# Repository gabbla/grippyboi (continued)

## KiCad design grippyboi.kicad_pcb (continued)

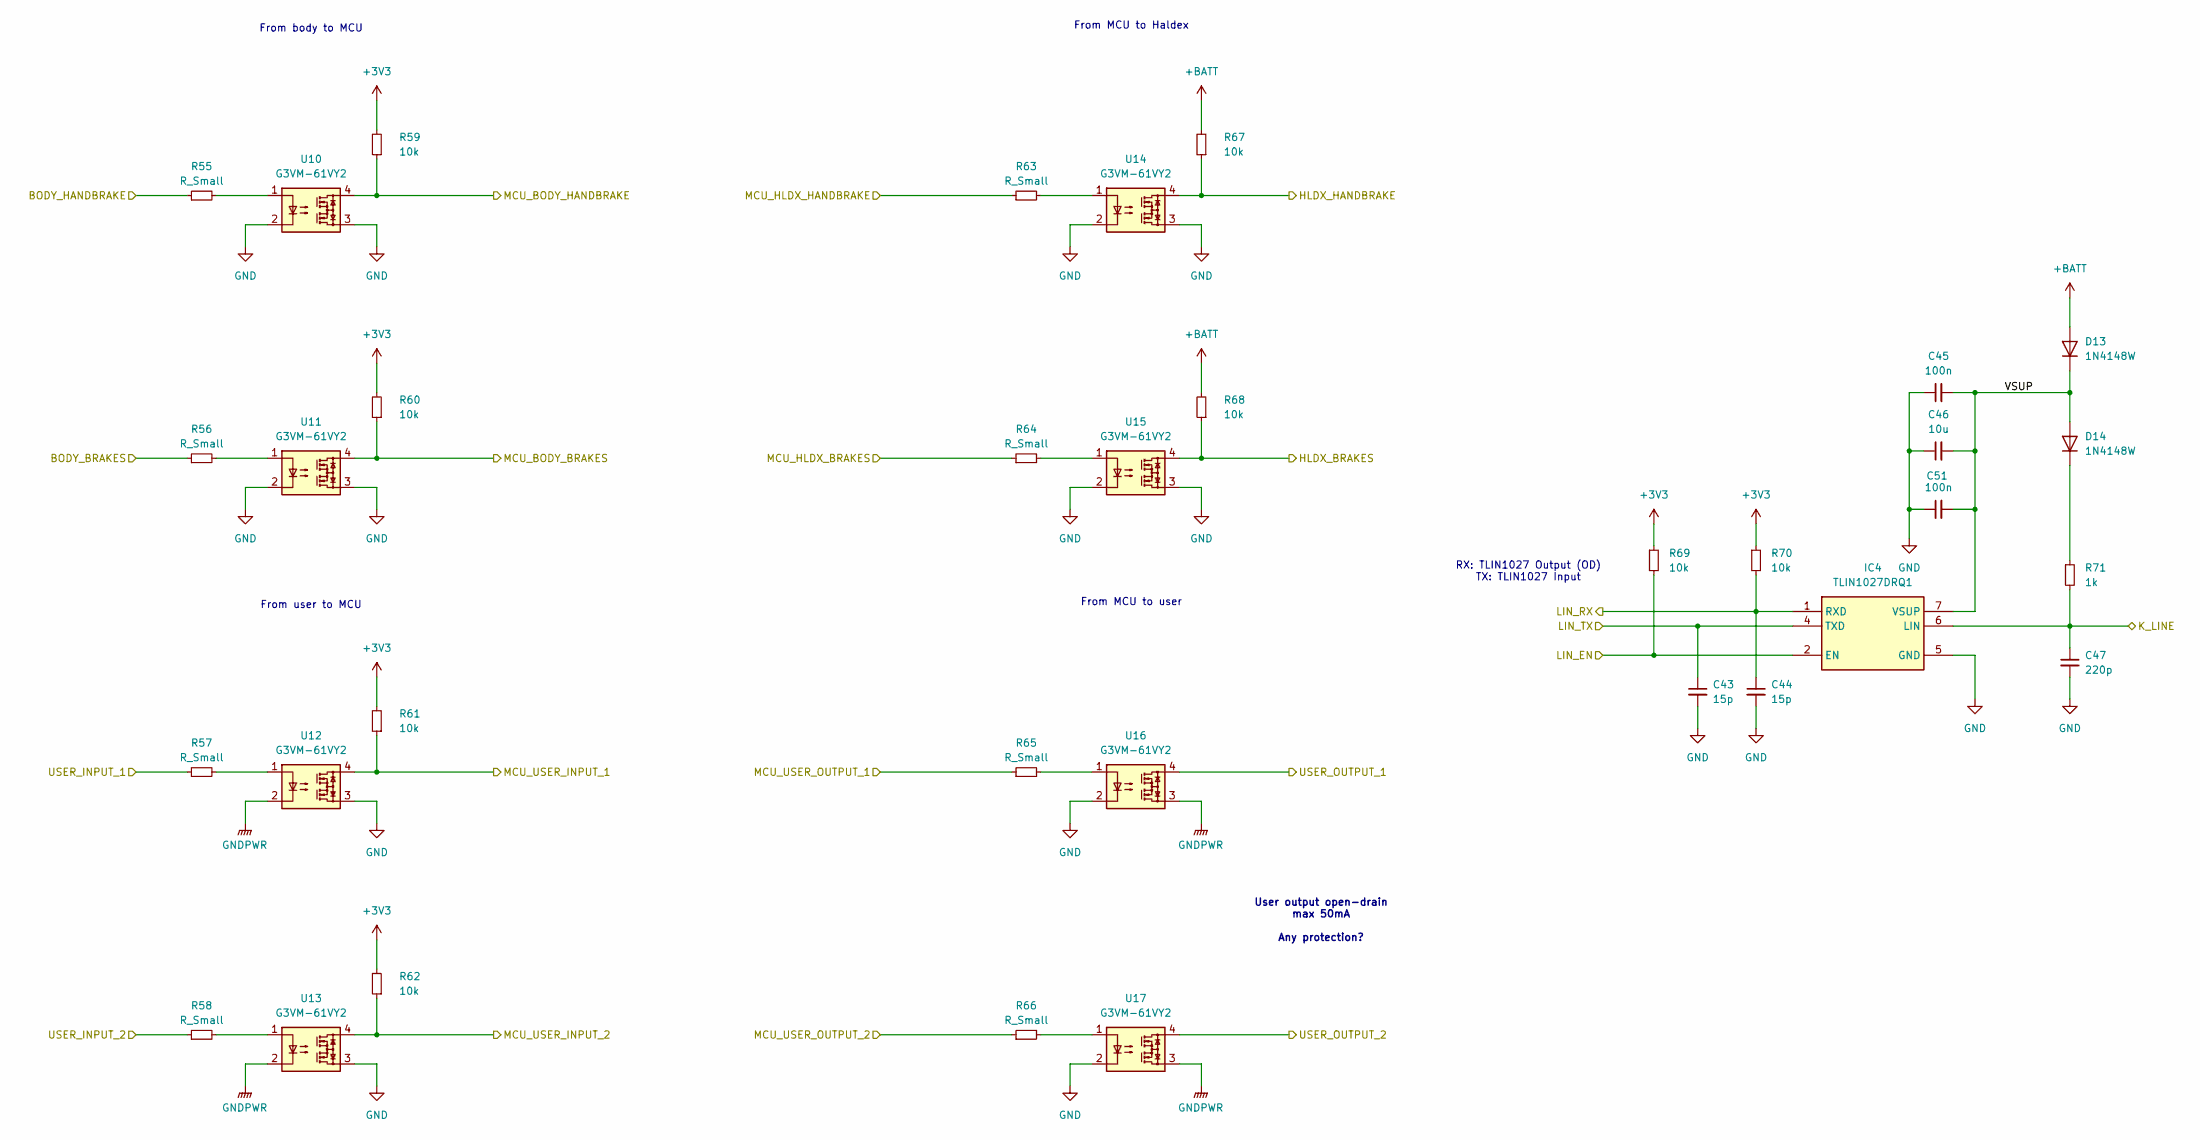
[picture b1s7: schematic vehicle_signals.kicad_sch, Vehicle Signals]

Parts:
C43, C44: 15p; C_0603_1608Metric_Pad1.08x0.95mm_HandSolder
C45, C51: 100n; C_0603_1608Metric_Pad1.08x0.95mm_HandSolder
C46: 10u; C_0603_1608Metric_Pad1.08x0.95mm_HandSolder
C47: 220p; C_0603_1608Metric_Pad1.08x0.95mm_HandSolder
D13, D14: 1N4148W; D_SOD-123
IC4: TLIN1027DRQ1; SOIC127P600X175-8N; Manufacturer_Part_Number TLIN1027DRQ1; Mouser Part Number 595-TLIN1027DRQ1
R55, R56, R57, R58, R63, R64, R65, R66: R_Small; R_0603_1608Metric_Pad0.98x0.95mm_HandSolder
R59, R60, R61, R62, R67, R68, R69, R70: 10k; R_0603_1608Metric_Pad0.98x0.95mm_HandSolder
R71: 1k; R_1206_3216Metric_Pad1.30x1.75mm_HandSolder
U10, U11, U12, U13, U14, U15, U16, U17: G3VM-61VY2; SOP254P700X230-4N

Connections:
+3V3: R59.2, R60.2, R61.2, R62.2, R69.1, R70.1; also elsewhere on the board
+BATT: D13.2 (A), R67.2, R68.2; also elsewhere on the board
/Connector/BODY_BRAKE_LIGHT_SWITCH: R56.1; also elsewhere on the board
/Connector/BODY_HANDBRAKE: R55.1; also elsewhere on the board
/Connector/HLDX_BRAKE_LIGHT_SWITCH: R68.1, U15.4; also elsewhere on the board
/Connector/HLDX_HANDBRAKE: R67.1, U14.4; also elsewhere on the board
/Connector/HLDX_K_LINE: C47.1, IC4.6 (LIN), R71.2; also elsewhere on the board
/Connector/USER_INPUT_1: R57.1; also elsewhere on the board
/Connector/USER_INPUT_2: R58.1; also elsewhere on the board
/Connector/USER_OUTPUT_1: U16.4; also elsewhere on the board
/Connector/USER_OUTPUT_2: U17.4; also elsewhere on the board
/MCU/LIN_EN: IC4.2 (EN), R69.2; also elsewhere on the board
/MCU/LIN_RX: C44.1, IC4.1 (RXD), R70.2; also elsewhere on the board
/MCU/LIN_TX: C43.1, IC4.4 (TXD); also elsewhere on the board
/MCU/MCU_BODY_BRAKES: R60.1, U11.4; also elsewhere on the board
/MCU/MCU_BODY_HANDBRAKE: R59.1, U10.4; also elsewhere on the board
/MCU/MCU_HLDX_BRAKES: R64.1; also elsewhere on the board
/MCU/MCU_HLDX_HANDBRAKE: R63.1; also elsewhere on the board
/MCU/MCU_USER_INPUT_1: R61.1, U12.4; also elsewhere on the board
/MCU/MCU_USER_INPUT_2: R62.1, U13.4; also elsewhere on the board
/MCU/MCU_USER_OUTPUT_1: R65.1; also elsewhere on the board
/MCU/MCU_USER_OUTPUT_2: R66.1; also elsewhere on the board
/Signals/VSUP: C45.2, C46.2, C51.2, D13.1 (K), D14.2 (A), IC4.7 (VSUP)
GND: C43.2, C44.2, C45.1, C46.1, C47.2, C51.1, IC4.5 (GND), U10.2, U10.3, U11.2, U11.3, U12.3, U13.3, U14.2, U14.3, U15.2, U15.3, U16.2, U17.2; also elsewhere on the board
GNDPWR: U12.2, U13.2, U16.3, U17.3; also elsewhere on the board
unnamed: D14.1 (K), R71.1
unnamed: R55.2, U10.1
unnamed: R56.2, U11.1
unnamed: R57.2, U12.1
unnamed: R58.2, U13.1
unnamed: R63.2, U14.1
unnamed: R64.2, U15.1
unnamed: R65.2, U16.1
unnamed: R66.2, U17.1

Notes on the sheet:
From MCU to Haldex
From user to MCU
From MCU to user
User output open-drain max 50mA Any protection?
From body to MCU
RX: TLIN1027 Output (OD) TX: TLIN1027 Input

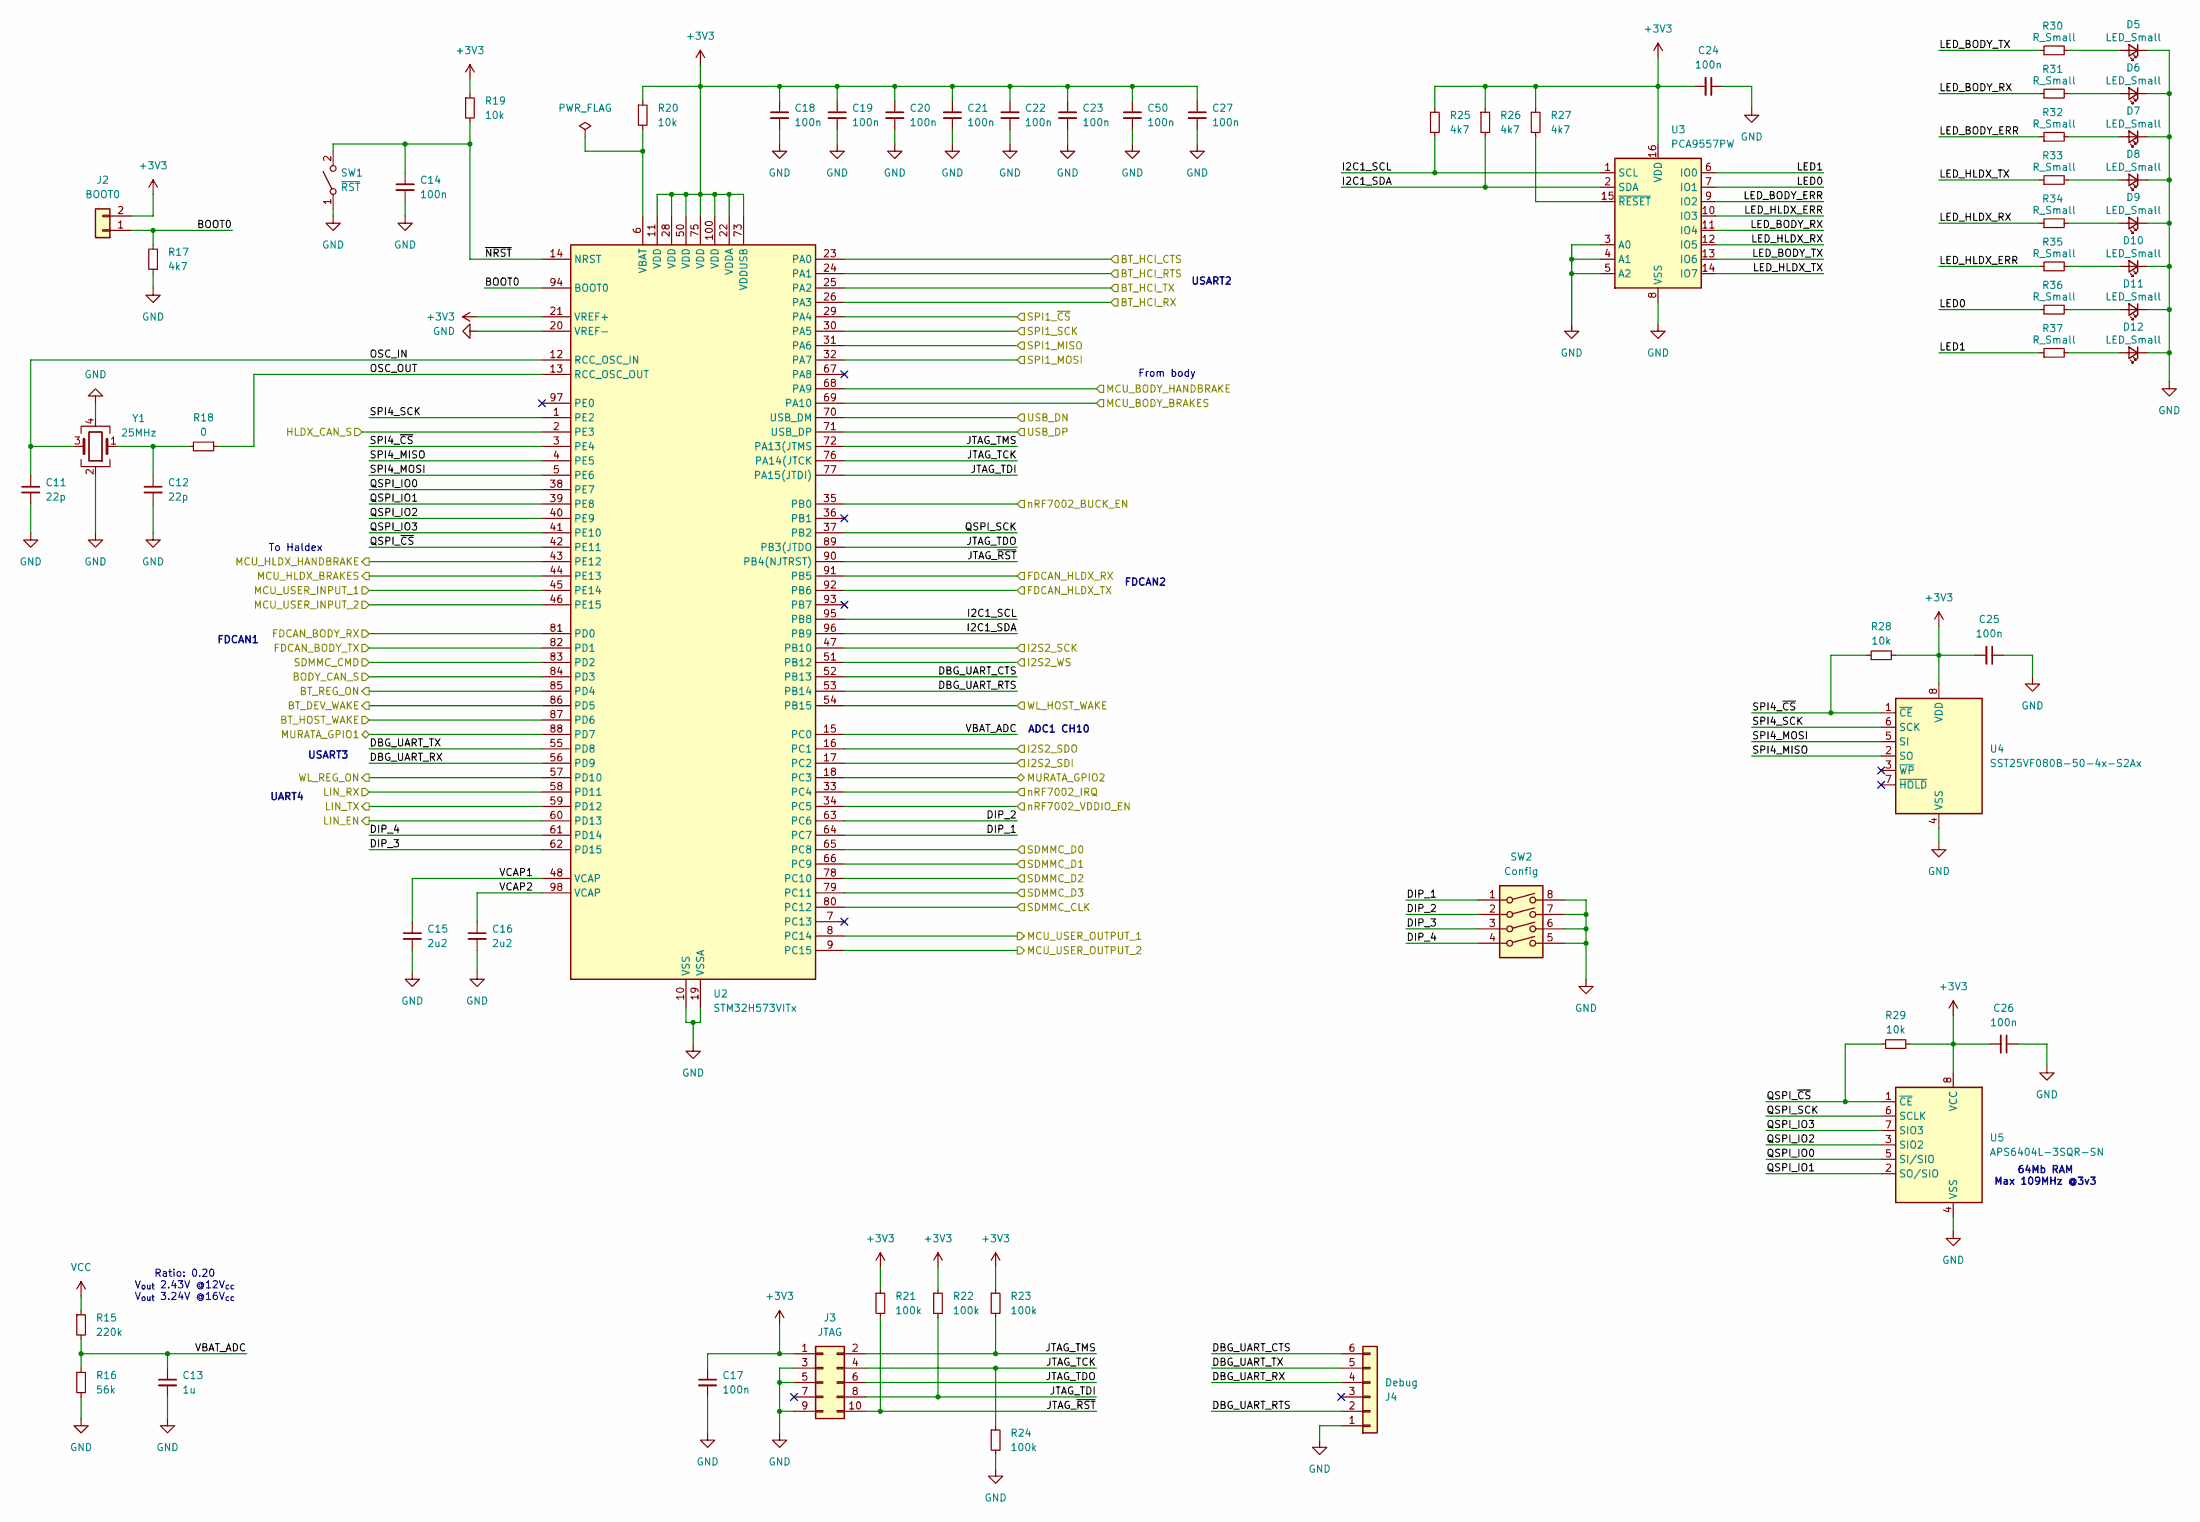
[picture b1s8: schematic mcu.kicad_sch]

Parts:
C11, C12: 22p; C_0603_1608Metric_Pad1.08x0.95mm_HandSolder
C13: 1u; C_0603_1608Metric_Pad1.08x0.95mm_HandSolder
C14, C17, C18, C19, C20, C21, C22, C23, C24, C25, C26, C27, C50: 100n; C_0603_1608Metric_Pad1.08x0.95mm_HandSolder
C15, C16: 2u2; C_0603_1608Metric_Pad1.08x0.95mm_HandSolder
D5, D6, D7, D8, D9, D10, D11, D12: LED_Small; LED_0603_1608Metric_Pad1.05x0.95mm_HandSolder
J2: BOOT0; PinHeader_1x02_P1.27mm_Vertical
J3: JTAG; PinHeader_2x05_P1.27mm_Vertical
J4: Debug; PinHeader_1x06_P2.54mm_Vertical
R15: 220k; R_0603_1608Metric_Pad0.98x0.95mm_HandSolder
R16: 56k; R_0603_1608Metric_Pad0.98x0.95mm_HandSolder
R17, R25, R26, R27: 4k7; R_0603_1608Metric_Pad0.98x0.95mm_HandSolder
R18: 0; R_0603_1608Metric_Pad0.98x0.95mm_HandSolder
R19, R20, R28, R29: 10k; R_0603_1608Metric_Pad0.98x0.95mm_HandSolder
R21, R22, R23, R24: 100k; R_0603_1608Metric_Pad0.98x0.95mm_HandSolder
R30, R31, R32, R33, R34, R35, R36, R37: R_Small; R_0603_1608Metric_Pad0.98x0.95mm_HandSolder
SW1: ~{RST}; SW_Push_SPST_NO_Alps_SKRK
SW2: Config; SW_DIP_SPSTx04_Slide_Copal_CHS-04A_W5.08mm_P1.27mm_JPin
U2: STM32H573VITx; LQFP-100_14x14mm_P0.5mm
U3: PCA9557PW; TSSOP-16_4.4x5mm_P0.65mm
U4: SST25VF080B-50-4x-S2Ax; SOIC-8_3.9x4.9mm_P1.27mm
U5: APS6404L-3SQR-SN; SOIC-8_3.9x4.9mm_P1.27mm
Y1: 25MHz; Crystal_SMD_3225-4Pin_3.2x2.5mm_HandSoldering

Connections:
+3V3: C17.1, C18.1, C19.1, C20.1, C21.1, C22.1, C23.1, C24.2, C25.2, C26.2, C27.1, C50.1, J2.2, J3.1, R19.1, R20.1, R21.1, R22.1, R23.1, R25.1, R26.1, R27.1, R28.2, R29.2, U2.11 (VDD), U2.21 (VREF+), U2.22 (VDDA), U2.28 (VDD), U2.50 (VDD), U2.73 (VDDUSB), U2.75 (VDD), U2.100 (VDD), U3.16 (VDD), U4.8 (VDD), U5.8 (VCC); also elsewhere on the board
/CAN PHYs/BODY_CAN_RX: U2.81 (PD0); also elsewhere on the board
/CAN PHYs/BODY_CAN_S: U2.84 (PD3); also elsewhere on the board
/CAN PHYs/BODY_CAN_TX: U2.82 (PD1); also elsewhere on the board
/CAN PHYs/HLDX_CAN_RX: U2.91 (PB5); also elsewhere on the board
/CAN PHYs/HLDX_CAN_S: U2.2 (PE3); also elsewhere on the board
/CAN PHYs/HLDX_CAN_TX: U2.92 (PB6); also elsewhere on the board
/MCU/BOOT0: J2.1, R17.2, U2.94 (BOOT0)
/MCU/BT_DEV_WAKE: U2.86 (PD5); also elsewhere on the board
/MCU/BT_HCI_CTS: U2.23 (PA0); also elsewhere on the board
/MCU/BT_HCI_RTS: U2.24 (PA1); also elsewhere on the board
/MCU/BT_HCI_RX: U2.26 (PA3); also elsewhere on the board
/MCU/BT_HCI_TX: U2.25 (PA2); also elsewhere on the board
/MCU/BT_HOST_WAKE: U2.87 (PD6); also elsewhere on the board
/MCU/BT_REG_ON: U2.85 (PD4); also elsewhere on the board
/MCU/DBG_UART_CTS: J4.6, U2.52 (PB13)
/MCU/DBG_UART_RTS: J4.2, U2.53 (PB14)
/MCU/DBG_UART_RX: J4.4, U2.56 (PD9)
/MCU/DBG_UART_TX: J4.5, U2.55 (PD8)
/MCU/DIP_1: SW2.1, U2.64 (PC7)
/MCU/DIP_2: SW2.2, U2.63 (PC6)
/MCU/DIP_3: SW2.3, U2.62 (PD15)
/MCU/DIP_4: SW2.4, U2.61 (PD14)
/MCU/I2C1_SCL: R25.2, U2.95 (PB8), U3.1 (SCL)
/MCU/I2C1_SDA: R26.2, U2.96 (PB9), U3.2 (SDA)
/MCU/I2S2_SCK: U2.47 (PB10); also elsewhere on the board
/MCU/I2S2_SDI: U2.17 (PC2); also elsewhere on the board
/MCU/I2S2_SDO: U2.16 (PC1); also elsewhere on the board
/MCU/I2S2_WS: U2.51 (PB12); also elsewhere on the board
/MCU/JTAG_TCK: J3.4, R24.1, U2.76 (PA14(JTCK)
/MCU/JTAG_TDI: J3.8, R22.2, U2.77 (PA15(JTDI))
/MCU/JTAG_TDO: J3.6, U2.89 (PB3(JTDO)
/MCU/JTAG_TMS: J3.2, R23.2, U2.72 (PA13(JTMS)
/MCU/JTAG_~RST: J3.10, R21.2, U2.90 (PB4(NJTRST))
/MCU/LED0: R36.1, U3.7 (IO1)
/MCU/LED1: R37.1, U3.6 (IO0)
/MCU/LED_BODY_ERR: R32.1, U3.9 (IO2)
/MCU/LED_BODY_RX: R31.1, U3.11 (IO4)
/MCU/LED_BODY_TX: R30.1, U3.13 (IO6)
/MCU/LED_HLDX_ERR: R35.1, U3.10 (IO3)
/MCU/LED_HLDX_RX: R34.1, U3.12 (IO5)
/MCU/LED_HLDX_TX: R33.1, U3.14 (IO7)
/MCU/LIN_EN: U2.60 (PD13); also elsewhere on the board
/MCU/LIN_RX: U2.58 (PD11); also elsewhere on the board
/MCU/LIN_TX: U2.59 (PD12); also elsewhere on the board
/MCU/MCU_BODY_BRAKES: U2.69 (PA10); also elsewhere on the board
/MCU/MCU_BODY_HANDBRAKE: U2.68 (PA9); also elsewhere on the board
/MCU/MCU_HLDX_BRAKES: U2.44 (PE13); also elsewhere on the board
/MCU/MCU_HLDX_HANDBRAKE: U2.43 (PE12); also elsewhere on the board
/MCU/MCU_USER_INPUT_1: U2.45 (PE14); also elsewhere on the board
/MCU/MCU_USER_INPUT_2: U2.46 (PE15); also elsewhere on the board
/MCU/MCU_USER_OUTPUT_1: U2.8 (PC14); also elsewhere on the board
/MCU/MCU_USER_OUTPUT_2: U2.9 (PC15); also elsewhere on the board
/MCU/MURATA_GPIO1: U2.88 (PD7); also elsewhere on the board
/MCU/MURATA_GPIO2: U2.18 (PC3); also elsewhere on the board
/MCU/OSC_IN: C11.1, U2.12 (RCC_OSC_IN), Y1.3
/MCU/OSC_OUT: R18.1, U2.13 (RCC_OSC_OUT)
/MCU/QSPI_IO0: U2.38 (PE7), U5.5 (SI/SIO)
/MCU/QSPI_IO1: U2.39 (PE8), U5.2 (SO/SIO)
/MCU/QSPI_IO2: U2.40 (PE9), U5.3 (SIO2)
/MCU/QSPI_IO3: U2.41 (PE10), U5.7 (SIO3)
/MCU/QSPI_SCK: U2.37 (PB2), U5.6 (SCLK)
/MCU/QSPI_~CS: R29.1, U2.42 (PE11), U5.1 (~CE)
/MCU/SDMMC_CLK: U2.80 (PC12); also elsewhere on the board
/MCU/SDMMC_CMD: U2.83 (PD2); also elsewhere on the board
/MCU/SDMMC_D0: U2.65 (PC8); also elsewhere on the board
/MCU/SDMMC_D1: U2.66 (PC9); also elsewhere on the board
/MCU/SDMMC_D2: U2.78 (PC10); also elsewhere on the board
/MCU/SDMMC_D3: U2.79 (PC11); also elsewhere on the board
/MCU/SPI1_MISO: U2.31 (PA6); also elsewhere on the board
/MCU/SPI1_MOSI: U2.32 (PA7); also elsewhere on the board
/MCU/SPI1_SCK: U2.30 (PA5); also elsewhere on the board
/MCU/SPI1_~CS: U2.29 (PA4); also elsewhere on the board
/MCU/SPI4_MISO: U2.4 (PE5), U4.2 (SO)
/MCU/SPI4_MOSI: U2.5 (PE6), U4.5 (SI)
/MCU/SPI4_SCK: U2.1 (PE2), U4.6 (SCK)
/MCU/SPI4_~CS: R28.1, U2.3 (PE4), U4.1 (~CE)
/MCU/USB_DN: U2.70 (USB_DM); also elsewhere on the board
/MCU/USB_DP: U2.71 (USB_DP); also elsewhere on the board
/MCU/VBAT_ADC: C13.1, R15.2, R16.1, U2.15 (PC0)
/MCU/VCAP1: C15.1, U2.48 (VCAP)
/MCU/VCAP2: C16.1, U2.98 (VCAP)
/MCU/WL_HOST_WAKE: U2.54 (PB15); also elsewhere on the board
/MCU/WL_REG_ON: U2.57 (PD10); also elsewhere on the board
/MCU/nRF7002_BUCK_EN: U2.35 (PB0); also elsewhere on the board
/MCU/nRF7002_IRQ: U2.33 (PC4); also elsewhere on the board
/MCU/nRF7002_VDDIO_EN: U2.34 (PC5); also elsewhere on the board
/MCU/~NRST: C14.1, R19.2, SW1.2 (B), U2.14 (NRST)
GND: C11.2, C12.2, C13.2, C14.2, C15.2, C16.2, C17.2, C18.2, C19.2, C20.2, C21.2, C22.2, C23.2, C24.1, C25.1, C26.1, C27.2, C50.2, D5.1 (K), D6.1 (K), D7.1 (K), D8.1 (K), D9.1 (K), D10.1 (K), D11.1 (K), D12.1 (K), J3.3, J3.5, J3.9, J4.1, R16.2, R17.1, R24.2, SW1.1 (A), SW2.5, SW2.6, SW2.7, SW2.8, U2.10 (VSS), U2.19 (VSSA), U2.20 (VREF-), U2.27 (VSS), U2.49 (VSS), U2.74 (VSS), U2.99 (VSS), U3.3 (A0), U3.4 (A1), U3.5 (A2), U3.8 (VSS), U4.4 (VSS), U5.4 (VSS), Y1.2, Y1.4; also elsewhere on the board
unnamed: C12.1, R18.2, Y1.1
unnamed: D5.2 (A), R30.2
unnamed: D6.2 (A), R31.2
unnamed: D7.2 (A), R32.2
unnamed: D8.2 (A), R33.2
unnamed: D9.2 (A), R34.2
unnamed: D10.2 (A), R35.2
unnamed: D11.2 (A), R36.2
unnamed: D12.2 (A), R37.2
unnamed: R20.2, U2.6 (VBAT)
unnamed: R27.2, U3.15 (~RESET)
VCC: R15.1; also elsewhere on the board

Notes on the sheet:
ADC1 CH10
Ratio: 0.20 V_{out} 2.43V @12V_{cc} V_{out} 3.24V @16V_{cc}
UART4
FDCAN1
From body
FDCAN2
USART3
64Mb RAM Max 109MHz @3v3
To Haldex
USART2

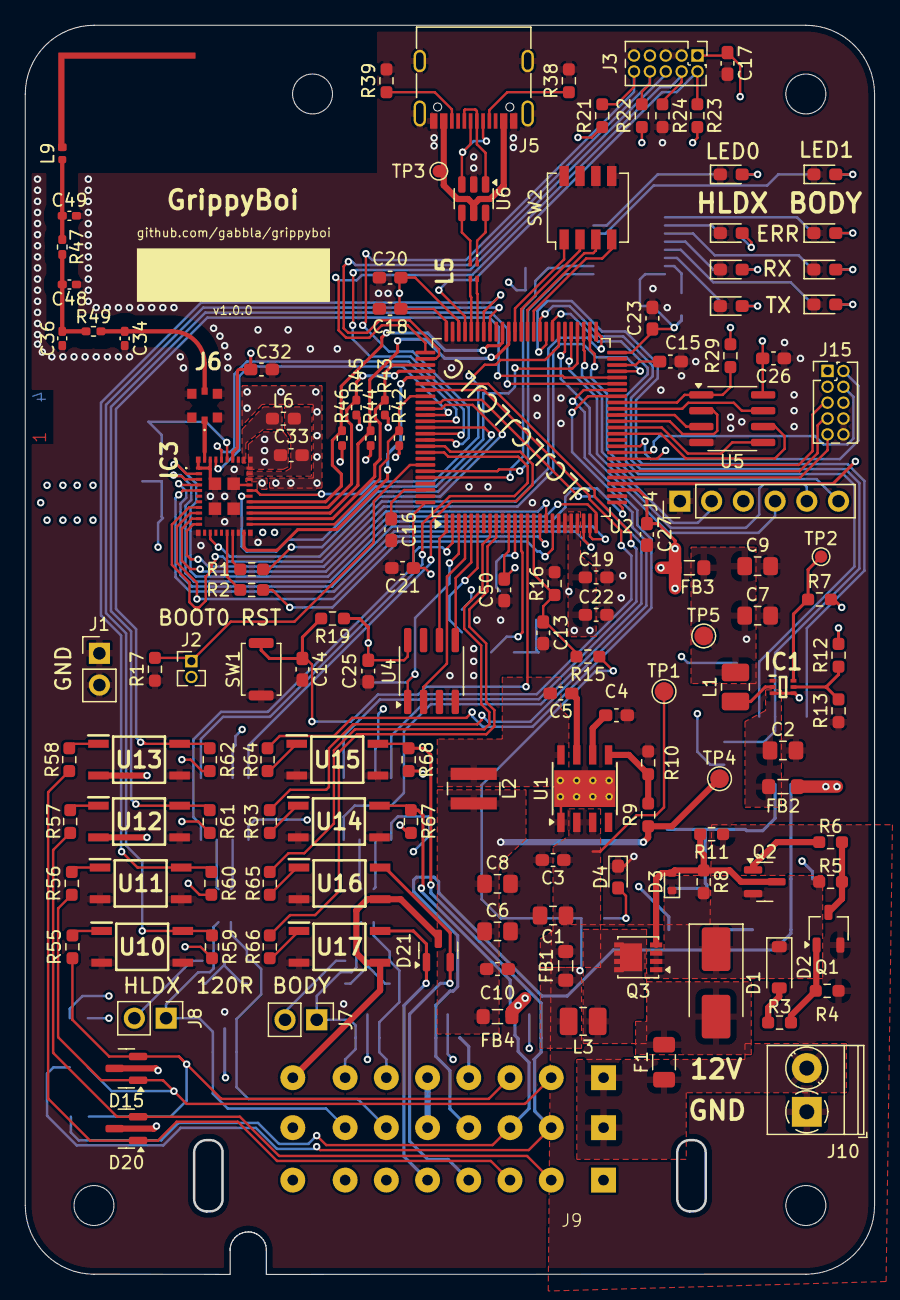
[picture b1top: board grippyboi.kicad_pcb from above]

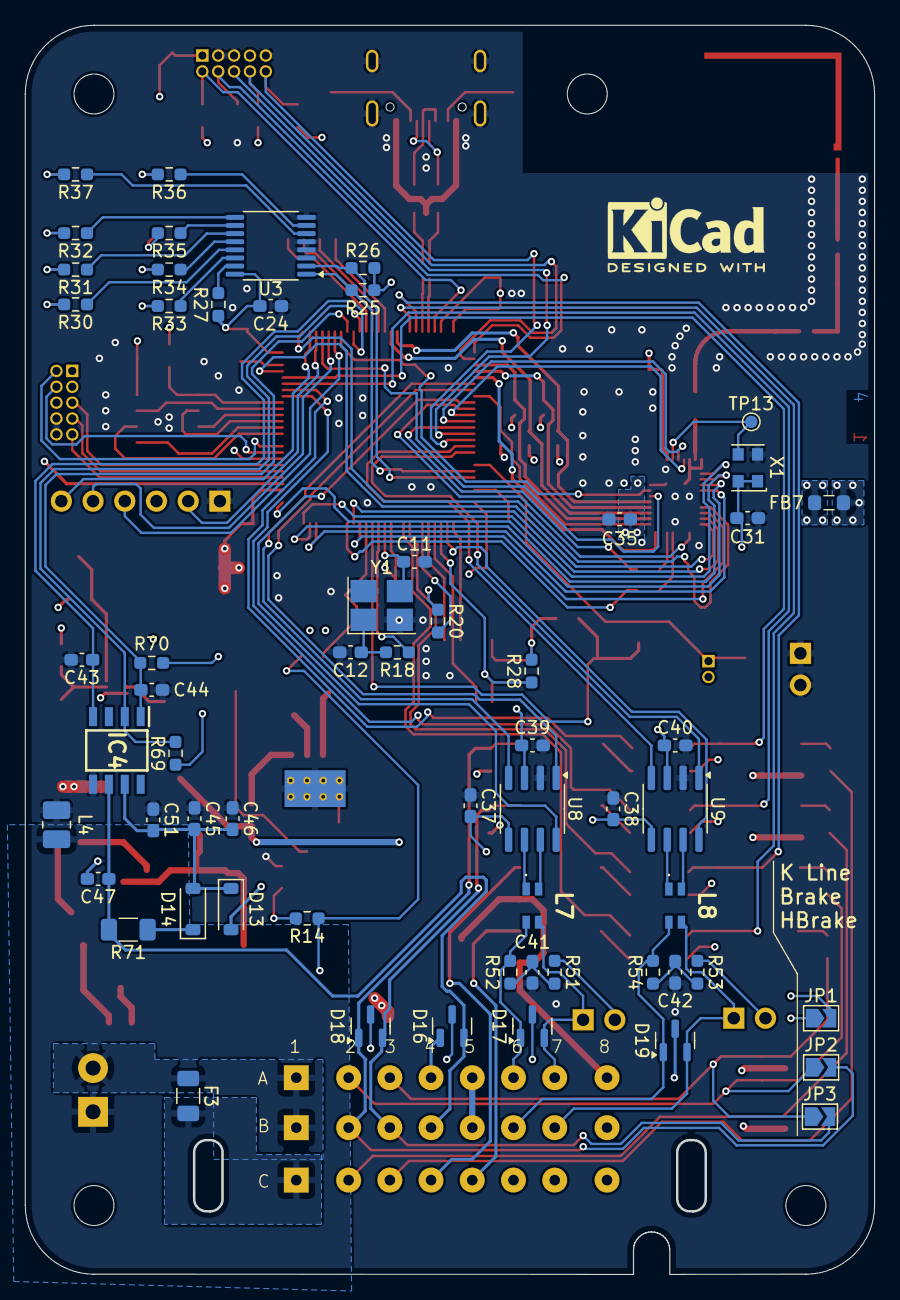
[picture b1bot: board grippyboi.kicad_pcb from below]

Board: 4 copper layers, 67.9 x 99.9 mm, 203 parts (60 on the bottom side), 176 nets.

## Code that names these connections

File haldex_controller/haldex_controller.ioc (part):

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Mcu.Name=STM32H573VITx
Mcu.Package=LQFP100
Mcu.UserName=STM32H573VITx
PA0.GPIOParameters=GPIO_Label
PA0.GPIO_Label=BT_HCI_CTS
PA0.Mode=CTS_RTS
PA0.Signal=USART2_CTS
PA1.GPIOParameters=GPIO_Label
PA1.GPIO_Label=BT_HCI_RTS
PA1.Mode=CTS_RTS
PA1.Signal=USART2_RTS
PA10.GPIOParameters=GPIO_Label
PA10.GPIO_Label=MCU_BRAKES
PA10.Signal=GPIO_Input
PA11.Mode=Device
PA11.Signal=USB_DM
PA12.Mode=Device
PA12.Signal=USB_DP
PA13(JTMS/SWDIO).Mode=JTAG_5_pins
PA13(JTMS/SWDIO).Signal=DEBUG_JTMS-SWDIO
PA14(JTCK/SWCLK).Mode=JTAG_5_pins
PA14(JTCK/SWCLK).Signal=DEBUG_JTCK-SWCLK
PA15(JTDI).Mode=JTAG_5_pins
PA15(JTDI).Signal=DEBUG_JTDI
PA2.GPIOParameters=GPIO_Label
PA2.GPIO_Label=BT_HCI_TX
PA2.Mode=Asynchronous
PA2.Signal=USART2_TX
PA3.GPIOParameters=GPIO_Label
PA3.GPIO_Label=BT_HCI_RX
PA3.Mode=Asynchronous
PA3.Signal=USART2_RX
PA4.Mode=NSS_Signal_Hard_Output
PA4.Signal=SPI1_NSS
PA5.Mode=Full_Duplex_Master
PA5.Signal=SPI1_SCK
PA6.Mode=Full_Duplex_Master
PA6.Signal=SPI1_MISO
PA7.Mode=Full_Duplex_Master
PA7.Signal=SPI1_MOSI
PA9.GPIOParameters=GPIO_Label
PA9.GPIO_Label=MCU_HANDBRAKE
PA9.Signal=GPIO_Input
PB0.GPIOParameters=GPIO_Label
PB0.GPIO_Label=nrf7002_BUCK_EN
PB0.Signal=GPIO_Input
PB10.Mode=Full_Duplex_Master
PB10.Signal=I2S2_CK
PB12.Mode=Full_Duplex_Master
PB12.Signal=I2S2_WS
PB13.Mode=CTS_RTS
PB13.Signal=USART3_CTS
PB14.Mode=CTS_RTS
PB14.Signal=USART3_RTS
PB15.GPIOParameters=GPIO_Label
PB15.GPIO_Label=WL_HOST_WAKE
PB15.Signal=GPIO_Input
PB2.Signal=OCTOSPI1_CLK
PB3(JTDO/TRACESWO).Mode=JTAG_5_pins
PB3(JTDO/TRACESWO).Signal=DEBUG_JTDO-SWO
PB4(NJTRST).Mode=JTAG_5_pins
PB4(NJTRST).Signal=DEBUG_JTRST
PB5.Mode=FDCAN_Activate
PB5.Signal=FDCAN2_RX
PB6.Mode=FDCAN_Activate
PB6.Signal=FDCAN2_TX
PB7.GPIOParameters=GPIO_Label
PB7.GPIO_Label=HLDX CAN S
PB7.Signal=GPIO_Output
PB8.Mode=I2C
PB8.Signal=I2C1_SCL
PB9.Mode=I2C
PB9.Signal=I2C1_SDA
PC0.GPIOParameters=GPIO_Label
PC0.GPIO_Label=VBAT_ADC
PC0.Signal=ADCx_INP10
PC1.Mode=Full_Duplex_Master
PC1.Signal=I2S2_SDO
PC10.Mode=SD_4_bits_Wide_bus
PC10.Signal=SDMMC1_D2
PC11.Mode=SD_4_bits_Wide_bus
PC11.Signal=SDMMC1_D3
PC12.Mode=SD_4_bits_Wide_bus
PC12.Signal=SDMMC1_CK
PC14-OSC32_IN(OSC32_IN).GPIOParameters=GPIO_Label
PC14-OSC32_IN(OSC32_IN).GPIO_Label=MCU_USER_OUTPUT_1
PC14-OSC32_IN(OSC32_IN).Signal=GPIO_Output
PC15-OSC32_OUT(OSC32_OUT).GPIOParameters=GPIO_Label
PC15-OSC32_OUT(OSC32_OUT).GPIO_Label=MCU_USER_OUTPUT_2
PC15-OSC32_OUT(OSC32_OUT).Signal=GPIO_Output
PC2.Mode=Full_Duplex_Master
PC2.Signal=I2S2_SDI
PC3.GPIOParameters=GPIO_Label
PC3.GPIO_Label=MURATA_GPIO2
PC3.Signal=GPIO_Input
PC4.GPIOParameters=GPIO_Label
PC4.GPIO_Label=nRF7002_IRQ
PC4.Signal=GPIO_Output
PC5.GPIOParameters=GPIO_Label
PC5.GPIO_Label=nRF7002_VDDIO_EN
PC5.Signal=GPIO_Output
PC6.GPIOParameters=GPIO_Label
PC6.GPIO_Label=DIP_2
PC6.Signal=GPIO_Input
PC7.GPIOParameters=GPIO_Label
PC7.GPIO_Label=DIP_1
PC7.Signal=GPIO_Input
PC8.Mode=SD_4_bits_Wide_bus
PC8.Signal=SDMMC1_D0
PC9.Mode=SD_4_bits_Wide_bus
PC9.Signal=SDMMC1_D1
PD0.Mode=FDCAN_Activate
PD0.Signal=FDCAN1_RX
PD1.Mode=FDCAN_Activate
PD1.Signal=FDCAN1_TX
PD10.GPIOParameters=GPIO_Label
PD10.GPIO_Label=WL_REG_ON
PD10.Signal=GPIO_Output
PD11.GPIOParameters=GPIO_Label
PD11.GPIO_Label=LIN_RX
PD11.Mode=Asynchronous
PD11.Signal=UART4_RX
PD12.GPIOParameters=GPIO_Label
PD12.GPIO_Label=LIN_TX
PD12.Mode=Asynchronous
PD12.Signal=UART4_TX
PD13.GPIOParameters=GPIO_Label
PD13.GPIO_Label=LIN_EN
PD13.Signal=GPIO_Output
PD14.GPIOParameters=GPIO_Label
PD14.GPIO_Label=DIP_4
PD14.Signal=GPIO_Input
PD15.GPIOParameters=GPIO_Label
PD15.GPIO_Label=DIP_3
PD15.Signal=GPIO_Input
PD2.Mode=SD_4_bits_Wide_bus
PD2.Signal=SDMMC1_CMD
PD3.GPIOParameters=GPIO_Label
PD3.GPIO_Label=BODY CAN S
PD3.Signal=GPIO_Output
PD4.GPIOParameters=GPIO_Label
PD4.GPIO_Label=BT_REG_ON
PD4.Signal=GPIO_Output
PD5.GPIOParameters=GPIO_Label
PD5.GPIO_Label=BT_DEV_WAKE
PD5.Signal=GPIO_Output
PD6.GPIOParameters=GPIO_Label
PD6.GPIO_Label=BT_HOST_WAKE
PD6.Signal=GPIO_Input
PD7.GPIOParameters=GPIO_Label
PD7.GPIO_Label=MURATA_GPIO_1
PD7.Signal=GPIO_Input
PD8.Mode=Asynchronous
PD8.Signal=USART3_TX
PD9.Mode=Asynchronous
PD9.Signal=USART3_RX
PE10.Signal=OCTOSPI1_IO7
PE11.Signal=OCTOSPI1_NCS
PE12.GPIOParameters=GPIO_Label
PE12.GPIO_Label=SIM_HANDBRAKE
PE12.Signal=GPIO_Output
PE13.GPIOParameters=GPIO_Label
PE13.GPIO_Label=SIM_BRAKES
PE13.Signal=GPIO_Output
PE14.GPIOParameters=GPIO_Label
PE14.GPIO_Label=MCU_USER_INPUT_1
PE14.Signal=GPIO_Input
PE15.GPIOParameters=GPIO_Label
PE15.GPIO_Label=MCU_USER_INPUT_2
PE15.Signal=GPIO_Input
PE2.Mode=Full_Duplex_Master
PE2.Signal=SPI4_SCK
PE4.Mode=NSS_Signal_Hard_Output
PE4.Signal=SPI4_NSS
PE5.Mode=Full_Duplex_Master
PE5.Signal=SPI4_MISO
PE6.Mode=Full_Duplex_Master
PE6.Signal=SPI4_MOSI
PE7.Signal=OCTOSPI1_IO4
PE8.Signal=OCTOSPI1_IO5
PE9.Signal=OCTOSPI1_IO6
PH0-OSC_IN(PH0).Mode=HSE-External-Oscillator
PH0-OSC_IN(PH0).Signal=RCC_OSC_IN
PH1-OSC_OUT(PH1).Mode=HSE-External-Oscillator
PH1-OSC_OUT(PH1).Signal=RCC_OSC_OUT
RCC.HSE_VALUE=25000000
RCC.SYSCLKFreq_VALUE=250000000
RCC.SYSCLKSource=RCC_SYSCLKSOURCE_PLLCLK
board=custom

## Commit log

2025-03-12 drawings: added title and project name
2025-03-12 readme: added
2025-03-14 lib: ptr7002: footprint added
2025-03-14 sch: added UART4 note on LIN
2025-03-14 External RAM changed to APS6404L 64Mbit
2025-04-29 io, spi flash, stuff
2025-04-29 page info update
2025-04-29 power: removed FL1
2025-04-29 lib: added G3VM-61VY2 solid state relay
2025-04-29 vehicle signals: using solid state relais
2025-04-29 lib: ptr7002: fix NC pin as passives
2025-04-29 lib: various footprint added
2025-04-29 sch: fixing component footprints
2025-04-30 lib: ecu24: footprint added
2025-04-30 sch: added footprint association
2025-04-30 sch: fix association with mounting holes and sw1/sw2
2025-04-30 sch: fix footprint association for J6
2025-04-30 brd: import from sch
2025-04-30 working on component placement
2025-04-30 sch: J10 footprint update
2025-05-06 lib: added murata 1yn pcb antenna footprint
2025-05-06 lib: added MM8130 ufl connector
2025-05-06 brd: routing in progress
2025-05-07 lib: ecu24: fix edge cut
2025-05-07 git: ignore autogenerated production files
2025-05-07 brd: layout complete
2025-05-07 brd: add version
2025-05-07 git: ignore pdfs
2025-05-07 sch: update verision on pages
2025-05-07 prj: rename project to grippyboi
2025-05-07 brd: layer order marker added
2025-05-22 sch: fix handbrake/brake I/O
2025-05-22 changelog: added
